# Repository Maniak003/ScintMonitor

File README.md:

<!DOCTYPE html>
<html lang="en" data-color-mode="auto" data-light-theme="light" data-dark-theme="dark">
  <head>
    <meta charset="utf-8">
  </head>
    <body class="logged-in env-production page-responsive page-blob" style="word-wrap: break-word;">
      <p> Monitor based on gammaspectrometer</p>
      
    </body>
</html>

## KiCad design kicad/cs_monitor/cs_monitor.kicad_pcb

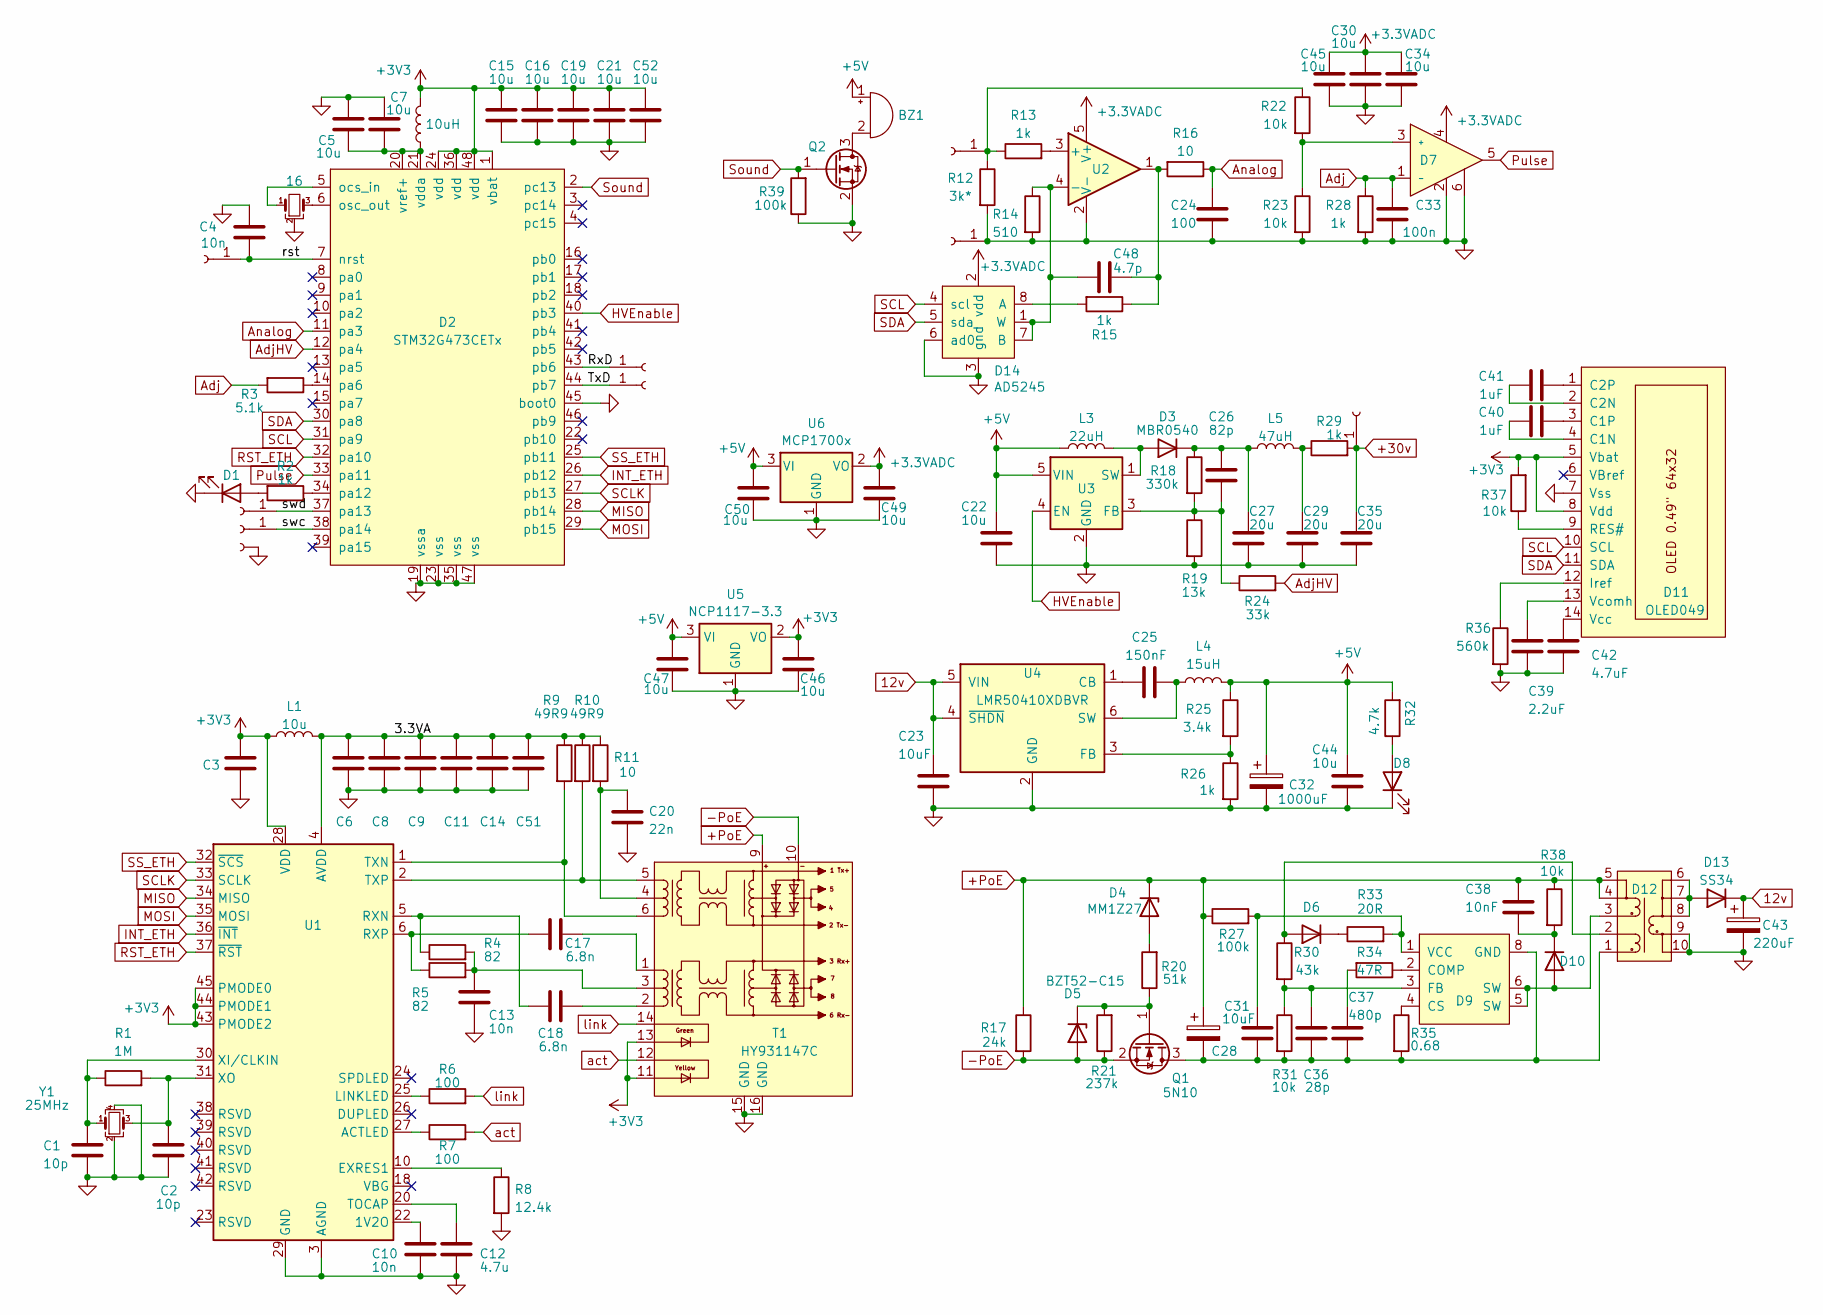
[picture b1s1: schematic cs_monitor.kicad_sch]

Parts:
BZ1: Buzzer; Buzzer_12x9.5RM7.6
C1, C2: 10p; C_0402_1005Metric
C3, C6, C8, C9, C11: 1u; C_0603_1608Metric
C4: 10n; C_0603_1608Metric
C5, C7, C15, C16, C19, C21, C30, C34, C45: 10u; C_0603_1608Metric
C10, C13: 10n; C_0402_1005Metric
C12: 4.7u; C_0402_1005Metric
C14, C51: 1u; C_0402_1005Metric
C17, C18: 6.8n; C_0402_1005Metric
C20: 22n; C_0402_1005Metric
C22, C44, C46, C47, C49, C50: 10u; C_0805_2012Metric
C23, C31: 10uF; C_0805_2012Metric
C24: 100; C_0603_1608Metric
C25: 150nF; C_0603_1608Metric
C26: 82p; C_0603_1608Metric
C27, C29, C35: 20u; C_1206_3216Metric
C28: 22uF/63v; CP_Elec_6.3x7.7
C32: 1000uF; CP_EIA-7343-15_Kemet-W
C33: 100n; C_0603_1608Metric
C36: 28p; C_0603_1608Metric
C37: 480p; C_0603_1608Metric
C38: 10nF; C_0603_1608Metric
C39: 2.2uF; C_0402_1005Metric
C40, C41: 1uF; C_0402_1005Metric
C42: 4.7uF; C_0402_1005Metric
C43: 220uF; CP_EIA-7343-15_Kemet-W
C48: 4.7p; C_0603_1608Metric
C52: 10u; C_0402_1005Metric
D1, D8: LED; LED_0603_1608Metric
D2: STM32G473CETx; LQFP-48_7x7mm_P0.5mm
D3: MBR0540; D_SOD-123
D4: MM1Z27; D_SOD-123
D5: BZT52-C15; D_SOD-123
D6, D10: F7; D_SOD-123
D7: TLV3501; SOT-23-6
D9: ?U6119SA?; SOIC-8-N7_3.9x4.9mm_P1.27mm
D11: OLED049
D12: ?T4932B?; DA2257
D13: SS34; D_SOD-123
D14: AD5245; SOT-23-8
J1, J2, J3, J5, J6, J7, J8, J9: Conn_01x01_Female; ConnMini
J4: Conn; ConnMini
L1: 10u; L_0805_2012Metric
L2: 10uH; L_0805_2012Metric
L3: 22uH; L_1206_3216Metric_Pad1.42x1.75mm_HandSolder
L4: 15uH; L_Abracon_ASPI-0630LR
L5: 47uH; L_0805_2012Metric
Q1: 5N10; SOT-23
Q2: Q_NMOS_GSD; SOT-23-3
R1: 1M; R_0402_1005Metric
R2, R13, R15, R26, R28, R29: 1k; R_0603_1608Metric
R3: 5.1k; R_0603_1608Metric
R4, R5: 82; R_0402_1005Metric
R6, R7: 100; R_0402_1005Metric
R8: 12.4k; R_0402_1005Metric
R9, R10: 49R9; R_0402_1005Metric
R11: 10; R_0402_1005Metric
R12: 3k*; R_0603_1608Metric
R14: 510; R_0603_1608Metric
R16: 10; R_0603_1608Metric
R17: 24k; R_0603_1608Metric
R18: 330k; R_0603_1608Metric
R19: 13k; R_0603_1608Metric
R20: 51k; R_0603_1608Metric
R21: 237k; R_0603_1608Metric
R22, R23, R31, R38: 10k; R_0603_1608Metric
R24: 33k; R_0603_1608Metric
R25: 3.4k; R_0603_1608Metric
R27, R39: 100k; R_0603_1608Metric
R30: 43k; R_0603_1608Metric
R32: 4.7k; R_0603_1608Metric
R33: 20R; R_0603_1608Metric
R34: 47R; R_0603_1608Metric
R35: 0.68; R_0603_1608Metric
R36: 560k; R_0402_1005Metric
R37: 10k; R_0402_1005Metric
T1: HY931147C
U1: W5500; LQFP-48_7x7mm_P0.5mm
U2: OPA354AIDBVR; TSOT-23-5
U3: LM2733XMF; SOT-23-5
U4: LMR50410XDBVR; SOT-23-6
U5: NCP1117-3.3; SOT-223-3_TabPin2
U6: MCP1700x; SOT-23
Y1: 25MHz; Crystal_SMD_3225-4Pin_3.2x2.5mm
Y2: 16; Resonator_SMD_Murata_CSTxExxV-3Pin_3.0x1.1mm

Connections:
12v: C23.1, C43.1, D13.1 (K), U4.4 (~SHDN), U4.5 (VIN)
+3.3VADC: C30.2, C34.2, C45.2, C49.2, D7.4, D14.2 (vdd), U2.5 (V+), U6.2 (VO)
+3V3: C3.1, C15.2, C16.2, C19.2, C21.2, C46.2, C52.2, D2.1 (vbat), D2.24 (vdd), D2.36 (vdd), D2.48 (vdd), D11.5 (Vbat), D11.8 (Vdd), L1.1, L2.2, R37.2, T1.11, T1.13, U1.28 (VDD), U1.43 (PMODE2), U1.44 (PMODE1), U1.45 (PMODE0), U5.2 (VO)
+5V: BZ1.1 (-), C22.2, C32.1, C44.2, C47.2, C50.2, L3.1, L4.2, R25.1, R32.2, U3.5 (VIN), U5.3 (VI), U6.3 (VI)
+30v: C35.2, J8.1, R29.2
+PoE: C28.1, C38.1, D4.1 (K), D12.4, D12.5, R17.1, R27.1, R38.1, T1.9
-PoE: D5.2 (A), Q1.2 (S), R17.2, R21.1, T1.10
/3.3VA: C6.1, C8.1, C9.1, C11.1, C14.1, C51.1, L1.2, R9.1, R10.1, R11.1, U1.4 (AVDD), U1.8 (AVDD), U1.11 (AVDD), U1.15 (AVDD), U1.17 (AVDD), U1.21 (AVDD)
/RxD: D2.43 (pb6), J5.1
/TxD: D2.44 (pb7), J6.1
/rst: C4.1, D2.7 (nrst), J1.1
/swc: D2.38 (pa14), J3.1
/swd: D2.37 (pa13), J2.1
Adj: C33.2, D7.1 (-), R3.2, R28.1
AdjHV: D2.12 (pa4), R24.2
Analog: C24.2, D2.11 (pa3), R16.1
GND: C1.2, C2.2, C3.2, C4.2, C5.2, C6.2, C7.2, C8.2, C9.2, C10.2, C11.2, C12.2, C13.2, C14.2, C15.1, C16.1, C19.1, C20.2, C21.1, C22.1, C23.2, C24.1, C27.1, C29.1, C30.1, C32.2, C33.1, C34.1, C35.1, C39.1, C42.1, C43.2, C44.1, C45.1, C46.1, C47.1, C49.1, C50.1, C51.2, C52.1, D1.1 (K), D2.19 (vssa), D2.23 (vss), D2.35 (vss), D2.45 (boot0), D2.47 (vss), D7.2, D7.6, D8.1 (K), D11.7 (Vss), D12.9, D12.10, D14.3 (gnd), D14.6 (ad0), J4.1, J9.1, Q2.2 (S), R8.2, R12.2, R14.2, R19.2, R23.2, R26.2, R28.2, R36.2, R39.1, T1.15 (GND), T1.16 (GND), U1.3 (AGND), U1.9 (AGND), U1.14 (AGND), U1.16 (AGND), U1.19 (AGND), U1.29 (GND), U1.48 (AGND), U2.2 (V-), U3.2 (GND), U4.2 (GND), U5.1 (GND), U6.1 (GND), Y1.2, Y1.4, Y2.2
HVEnable: D2.40 (pb3), U3.4 (EN)
INT_ETH: D2.26 (pb12), U1.36 (~INT)
MISO: D2.28 (pb14), U1.34 (MISO)
MOSI: D2.29 (pb15), U1.35 (MOSI)
unnamed: BZ1.2 (+), Q2.3 (D)
unnamed: C13.1, R4.2, R5.2, T1.3
unnamed: C17.2, T1.1
unnamed: C18.2, T1.2
unnamed: C20.1, R11.2, T1.4
unnamed: C29.2, L5.2, R29.1
unnamed: C37.1, R34.2
unnamed: C48.1, R15.1, R16.2, U2.1
unnamed: D1.2 (A), R2.2
unnamed: D2.5 (ocs_in), Y2.1
unnamed: D2.6 (osc_out), Y2.3
unnamed: D2.14 (pa6), R3.1
unnamed: D2.34 (pa12), R2.1
unnamed: C5.1, C7.1, D2.20 (vref+), D2.21 (vdda), L2.1
unnamed: D3.2 (A), L3.2, U3.1 (SW)
unnamed: C26.2, C27.2, D3.1 (K), L5.1, R18.1
unnamed: D4.2 (A), R20.2
unnamed: D5.1 (K), Q1.1 (G), R20.1, R21.2
unnamed: D6.2 (A), D12.2, R30.1
unnamed: D6.1 (K), R33.1
unnamed: D7.3 (+), R22.2, R23.1
unnamed: D8.2 (A), R32.1
unnamed: D9.2 (COMP), R34.1
unnamed: D9.4 (CS), R35.1
unnamed: C36.1, D9.3 (FB), R30.2, R31.1
unnamed: C28.2, C31.2, C36.2, C37.2, D9.8 (GND), D12.1, Q1.3 (D), R31.2, R35.2
unnamed: C31.1, D9.1 (VCC), R27.2, R33.2
unnamed: D9.5 (SW), D9.6 (SW), D10.2 (A), D12.3
unnamed: C38.2, D10.1 (K), R38.2
unnamed: C41.2, D11.4 (C1N)
unnamed: C41.1, D11.3 (C1P)
unnamed: C40.2, D11.2 (C2N)
unnamed: C40.1, D11.1 (C2P)
unnamed: D11.12 (Iref), R36.1
unnamed: D11.9 (RES#), R37.1
unnamed: C42.2, D11.14 (Vcc)
unnamed: C39.2, D11.13 (Vcomh)
unnamed: D12.6, D12.7, D12.8, D13.2 (A)
unnamed: D14.8 (A), R15.2
unnamed: C48.2, D14.1 (W), D14.7 (B), R14.1, U2.4 (-)
unnamed: J7.1, R12.1, R13.1, R22.1
unnamed: C10.1, U1.22 (1V2O)
unnamed: R7.1, U1.27 (ACTLED)
unnamed: R8.1, U1.10 (EXRES1)
unnamed: R6.1, U1.25 (LINKLED)
unnamed: C18.1, R4.1, U1.5 (RXN)
unnamed: C17.1, R5.1, U1.6 (RXP)
unnamed: C12.1, U1.20 (TOCAP)
unnamed: R9.2, T1.6, U1.1 (TXN)
unnamed: R10.2, T1.5, U1.2 (TXP)
unnamed: C1.1, R1.1, U1.30 (XI/CLKIN), Y1.1
unnamed: C2.1, R1.2, U1.31 (XO), Y1.3
unnamed: R13.2, U2.3 (+)
unnamed: C26.1, R18.2, R19.1, R24.1, U3.3 (FB)
unnamed: C25.1, U4.1 (CB)
unnamed: R25.2, R26.1, U4.3 (FB)
unnamed: C25.2, L4.1, U4.6 (SW)
Pulse: D2.33 (pa11), D7.5
RST_ETH: D2.32 (pa10), U1.37 (~RST)
SCL: D2.31 (pa9), D11.10 (SCL), D14.4 (scl)
SCLK: D2.27 (pb13), U1.33 (SCLK)
SDA: D2.30 (pa8), D11.11 (SDA), D14.5 (sda)
SS_ETH: D2.25 (pb11), U1.32 (~SCS)
Sound: D2.2 (pc13), Q2.1 (G), R39.2
act: R7.2, T1.12
link: R6.2, T1.14

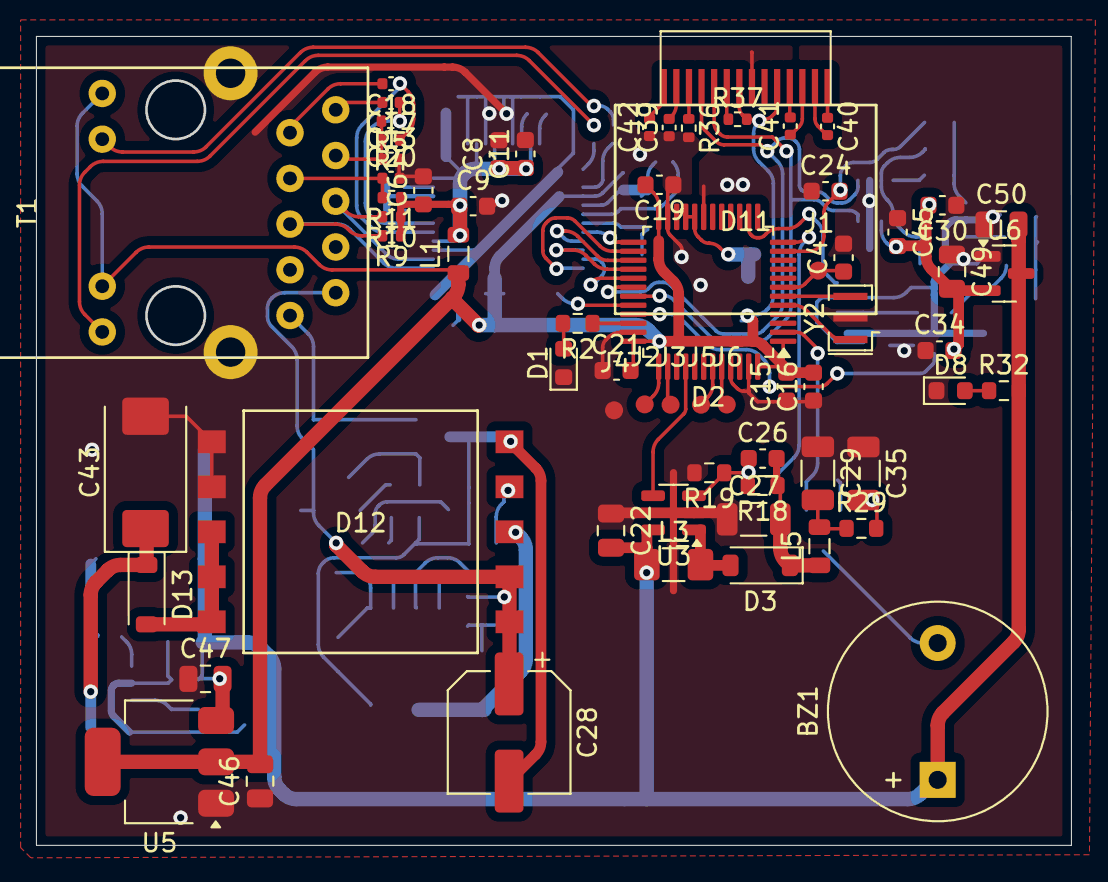
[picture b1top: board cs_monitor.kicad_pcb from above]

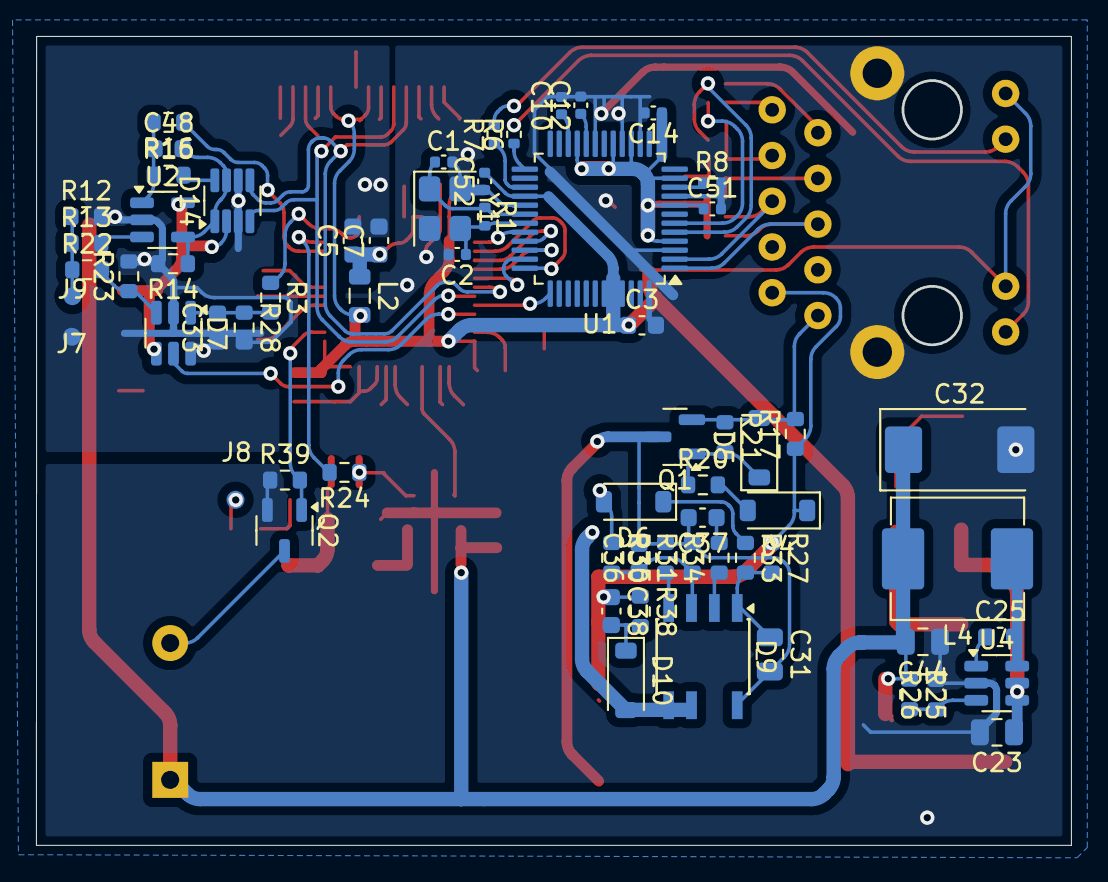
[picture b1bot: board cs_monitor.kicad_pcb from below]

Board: 2 copper layers, 57.5 x 44.9 mm, 131 parts (65 on the bottom side), 87 nets.

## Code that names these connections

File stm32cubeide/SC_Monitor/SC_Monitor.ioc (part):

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Mcu.Name=STM32G473C(B-C-E)Tx
Mcu.Package=LQFP48
Mcu.UserName=STM32G473CETx
PA10.GPIOParameters=GPIO_Label
PA10.GPIO_Label=W5500_RST
PA10.Signal=GPIO_Output
PA11.GPIOParameters=GPIO_Label
PA11.GPIO_Label=Pulse
PA11.Signal=GPXTI11
PA12.GPIOParameters=GPIO_Label
PA12.GPIO_Label=LED
PA12.Signal=GPIO_Output
PA3.GPIOParameters=GPIO_Label
PA3.GPIO_Label=AnalogIN
PA3.Mode=IN4-Single-Ended
PA3.Signal=ADC1_IN4
PA4.GPIOParameters=GPIO_Label
PA4.GPIO_Label=AdjHV
PA4.Signal=COMP_DAC11_group
PA6.GPIOParameters=GPIO_Label
PA6.GPIO_Label=AdjCOMP
PA6.Signal=COMP_DAC21_group
PA8.GPIOParameters=GPIO_Pu
PA8.GPIO_Pu=GPIO_PULLUP
PA8.Mode=I2C
PA8.Signal=I2C2_SDA
PA9.GPIOParameters=GPIO_Pu
PA9.GPIO_Pu=GPIO_PULLUP
PA9.Mode=I2C
PA9.Signal=I2C2_SCL
PB11.GPIOParameters=GPIO_Label
PB11.GPIO_Label=W5500_CS
PB11.Signal=GPIO_Output
PB12.GPIOParameters=GPIO_Label
PB12.GPIO_Label=ETH_INT
PB12.Signal=GPXTI12
PB13.GPIOParameters=GPIO_PuPd,GPIO_Label
PB13.GPIO_Label=W5500_SCK
PB13.GPIO_PuPd=GPIO_PULLUP
PB13.Mode=Full_Duplex_Master
PB13.Signal=SPI2_SCK
PB14.GPIOParameters=GPIO_PuPd,GPIO_Label
PB14.GPIO_Label=W5500_MISO
PB14.GPIO_PuPd=GPIO_PULLUP
PB14.Mode=Full_Duplex_Master
PB14.Signal=SPI2_MISO
PB15.GPIOParameters=GPIO_PuPd,GPIO_Label
PB15.GPIO_Label=W5500_MOSI
PB15.GPIO_PuPd=GPIO_PULLUP
PB15.Mode=Full_Duplex_Master
PB15.Signal=SPI2_MOSI
PB3.GPIOParameters=GPIO_Label
PB3.GPIO_Label=HVEnable
PB3.Signal=GPIO_Output
PB6.Mode=Asynchronous
PB6.Signal=USART1_TX
PB7.Mode=Asynchronous
PB7.Signal=USART1_RX
PC13.GPIOParameters=GPIO_Label
PC13.GPIO_Label=SOUND
PC13.Signal=GPIO_Output
PF0-OSC_IN.Mode=HSE-External-Oscillator
PF0-OSC_IN.Signal=RCC_OSC_IN
PF1-OSC_OUT.Mode=HSE-External-Oscillator
PF1-OSC_OUT.Signal=RCC_OSC_OUT
RCC.HSE_VALUE=16000000
RCC.SYSCLKFreq_VALUE=168000000
RCC.SYSCLKSource=RCC_SYSCLKSOURCE_PLLCLK
board=custom

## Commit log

2025-07-13 новый файл: Documents/scint_monitor.png новый файл: FreeCAD/CSMonitorHolder.FCStd новый файл: FreeCAD/CSMonitorHolder.FCStd1 новый файл: FreeCAD/CSMonitorHolder.stl новый файл: GNUPlot/Makefile новый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
2025-07-13 новый файл: Documents/Rad.png изменено: GNUPlot/alpha-01072025.dat изменено: GNUPlot/mainChart-1.gp удалено: kicad/cs_monitor/_autosave-cs_monitor.kicad_pcb удалено: kicad/cs_monitor/cs_monitor-backu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
2025-07-18 новый файл: Documents/Rad.png новый файл: Documents/W5500_ds_v110e.pdf новый файл: Documents/scint_monitor.png новый файл: FreeCAD/CSMonitorHolder.FCStd новый файл: FreeCAD/CSMonitorHolder.FCStd1 нов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
2025-07-18 удалено: kicad/cs_monitor/#auto_saved_files# удалено: kicad/cs_monitor/_autosave-cs_monitor.kicad_pcb удалено: kicad/cs_monitor/_autosave-cs_monitor.kicad_sch удалено: kicad/cs_monitor/cs_monitor-bac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
2025-07-18 новый файл: stm32cubeide/SC_Monitor/Core/Inc/webpages.h новый файл: stm32cubeide/SC_Monitor/Core/Src/webpages.c
2025-07-20 удалено: kicad/cs_monitor/cs_monitor-backups/cs_monitor-2025-07-08_184829.zip удалено: kicad/cs_monitor/cs_monitor-backups/cs_monitor-2025-07-08_185838.zip изменено: kicad/cs_monitor/cs_monitor.kicad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
2025-07-21 новый файл: kicad/cs_monitor/bom/ibom.html изменено: kicad/cs_monitor/cs_monitor.kicad_pcb изменено: kicad/cs_monitor/cs_monitor.kicad_sch изменено: stm32cubeide/SC_Monitor/.mxproject изменено: stm32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
2025-07-22 новый файл: Documents/web_interface.png изменено: kicad/cs_monitor/cs_monitor.kicad_prl изменено: kicad/cs_monitor/fp-info-cache изменено: stm32cubeide/SC_Monitor/Core/Inc/main.h изменено: stm32cubei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
2025-07-25 удалено: kicad/cs_monitor/cs_monitor-backups/cs_monitor-2025-07-08_190359.zip изменено: stm32cubeide/SC_Monitor/Core/Inc/main.h изменено: stm32cubeide/SC_Monitor/Core/Inc/networkint.h изменено: stm32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
2025-07-25 изменено: Documents/web_interface.png
2025-07-27 изменено: kicad/cs_monitor/cs_monitor.kicad_sch
2025-07-29 изменено: Documents/web_interface.png изменено: README.md изменено: stm32cubeide/SC_Monitor/Core/Inc/main.h изменено: stm32cubeide/SC_Monitor/Core/Inc/webpages.h изменено: stm32cubeide/SC_Monitor/Cor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
2025-07-29 удалено: kicad/cs_monitor/cs_monitor-backups/cs_monitor-2025-07-09_181433.zip удалено: kicad/cs_monitor/cs_monitor-backups/cs_monitor-2025-07-09_181946.zip изменено: kicad/cs_monitor/cs_monitor.kicad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
2025-07-30 удалено: kicad/cs_monitor/cs_monitor-backups/cs_monitor-2025-07-09_183647.zip удалено: kicad/cs_monitor/cs_monitor-backups/cs_monitor-2025-07-09_190248.zip изменено: kicad/cs_monitor/cs_monitor.kicad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
2025-07-30 удалено: kicad/cs_monitor/cs_monitor-backups/cs_monitor-2025-07-09_190842.zip удалено: kicad/cs_monitor/cs_monitor-backups/cs_monitor-2025-07-11_220437.zip удалено: kicad/cs_monitor/cs_monitor-backup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
2025-08-04 новый файл: stm32cubeide/SC_Monitor/Drivers/STM32G4xx_HAL_Driver/Inc/stm32g4xx_hal_tim.h новый файл: stm32cubeide/SC_Monitor/Drivers/STM32G4xx_HAL_Driver/Inc/stm32g4xx_hal_tim_ex.h новый файл: stm32c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
2025-09-14 изменено: stm32cubeide/SC_Monitor/.mxproject изменено: stm32cubeide/SC_Monitor/.settings/language.settings.xml изменено: stm32cubeide/SC_Monitor/Core/Inc/main.h изменено: stm32cubeide/SC_Monitor/Core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
2025-09-28 изменено: kicad/cs_monitor/cs_monitor.kicad_pcb изменено: kicad/cs_monitor/cs_monitor.kicad_sch изменено: stm32cubeide/SC_Monitor/Core/Inc/main.h изменено: stm32cubeide/SC_Monitor/Core/Src/main.c изм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
